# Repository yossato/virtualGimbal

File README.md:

# VirtualGimbal
The VirtualGimbal is an electronic stabilize device for videos that were taken by a hand-held camera such as a DSLR. For more information, see [PetaPixel] ( https://petapixel.com/2016/08/11/sd-card-built-gyro-sensor-stabilize-shots/ "PetaPixel").  The VirtualGimbal consists of an SD card and post-processing software. This repository releases the post-processing software, a SD card circuit and a SD card firmware.

## Demo
<https://youtu.be/NwUnrnFLjD4>

## Features
1.Post-processing video stabilization software on PC.  
2.4K video available.  
3.Stabilization completely based on captured angular velocity data.  

## Requirement
Ubuntu 18.04 or later
FFMPEG, OpenCV3, Eigen, boost and some python libraries.

## Usage  
See post_processing_software/README.md  
Download [Example Video](https://www.dropbox.com/s/y9ugb7c9l8qy5zy/C0003.MP4?dl=1), put in ~/vgdataset. Download [Angular Velocity data](https://www.dropbox.com/s/mz7mn3maapkgodw/2019-04-03_07.27.36.json?dl=1) and put it in virtualGimbal/post_processing_software/build/records. A camera calibration file also required to run a demo below so download [Calibration file](https://www.dropbox.com/s/we9r2a2w1un4lyf/cameras.json?dl=1) then put it in virtualGimbal/post_processing_software/build/camera_descriptions    

Demo:  
```
./pixelwise_stabilizer -i ~/vgdataset/C0003.MP4 -c ILCE-6500 -l SEL1670Z -j records/2019-04-03_07.27.36.json -z 1.3 -o  
```

Here, `i` option is an input video file. `c` is a camera name that is calibrated using a calibrator. `l` is a lens name. `j` is a json file that include an angular velocity record of a gyro sensor. `z` is a zooming ratio. Recommended zooming ratio is 1.3 . `o` option outputs stabilized video.  
Additional option `n` is available to disable preview window. This option speed ups the processing.    

Camera calibration is required before you stabilize your own video. See a [detail information](https://github.com/yossato/virtualGimbal/tree/master/post_processing_software) to do it.

## Install dependencies
### Install system dependencies:
```
sudo apt-get install cmake make git  
```

### Install Git:
```
sudo apt install git-all
```  

### Install Python Dev:
```
sudo apt-get install python3-dev python3-pip python3-tk python3-lxml python3-six
```

### Install Numpy & Scipy:
```
sudo apt-get install python3-numpy python3-scipy
```

### Install Matplot Library:
```
sudo apt-get install python3-matplotlib
```

### Install OpenCL: See [detail information](https://github.com/intel/compute-runtime/releases)
```
sudo apt install ocl-icd-libopencl1 opencl-headers clinfo ocl-icd-opencl-dev  

# OPTION: Install intel conpute-runtime with a command below if you use intel HD graphics.
# If you use NVIDIA gpu, it is not required. On the other hand, CUDA is required.
sudo apt-get install intel-opencl-icd
```

### Install ffmpeg:  
```
sudo apt install yasm pkg-config  
cd  
git clone  git://source.ffmpeg.org/ffmpeg.git  
cd ffmpeg
git checkout -b tag refs/tags/n4.4
./configure --enable-gpl --enable-x86asm --enable-opencl --enable-ffmpeg --enable-pic --enable-shared --disable-static --enable-swscale
make all -j4  
sudo make install  
sudo ldconfig  
```

### Install OpenCV  
```
cd  
sudo apt-get install build-essential module-assistant libgtk-3-dev  
sudo m-a prepare  
git clone https://github.com/opencv/opencv.git
cd opencv
git checkout refs/tags/4.5.3
cd opencv/  
  
mkdir build  
cd build  
cmake .. -DWITH_TBB=ON -DWITH_OPENGL=ON -DWITH_VTK=ON -DWITH_GTK=ON  -DWITH_FFMPEG=ON -DCMAKE_BUILD_TYPE=Release    
make -j4  
sudo make install  

sudo sh -c "echo /usr/local/lib >> /etc/ld.so.conf.d/opencv.conf"  
sudo sh -c "echo PKG_CONFIG_PATH=\\\$PKG_CONFIG_PATH:/usr/local/lib/pkgconfig >> /etc/bash.bashrc"  
sudo sh -c "echo export PKG_CONFIG_PATH >> /etc/bash.bashrc"  
```

### Install Eigen
```
sudo apt install libeigen3-dev  
```

## Build
```
cd
git clone https://github.com/yossato/virtualGimbal.git  
cd virtualGimbal  
mkdir build  
cd build  
cmake ../post_processing_software/ -DCMAKE_BUILD_TYPE=Release  
make -j4  
```

## To start up faster  
I added a program angular_velocity_estimator that generates a JSON file. The file will be saved in same directory of video file after execution.
If the file exists, the pixelwise_stabilizer starts up faster.
To run the program, execute a command like below.
```  
./angular_velocity_estimator ~/vgdataset/C0003.MP4  
```  
  
This command generates C0003.json .

The file contains estimated angular velocity from the video that is used for synchronizing between video and angular velocity measured by the gyro sensor.

## Contribution

## Todo
- Speeding up
- Brushing up deblur quality

## Author
Yoshiaki Sato

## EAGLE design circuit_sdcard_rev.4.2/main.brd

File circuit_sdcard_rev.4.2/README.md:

## License  
Copyright (c) 2018, Yoshiaki Sato  
<br />This work is licensed under a <a rel="license" href="http://creativecommons.org/licenses/by-sa/4.0/">Creative Commons Attribution-ShareAlike 4.0 International License</a>.  

# This circuit is SD card virsion.

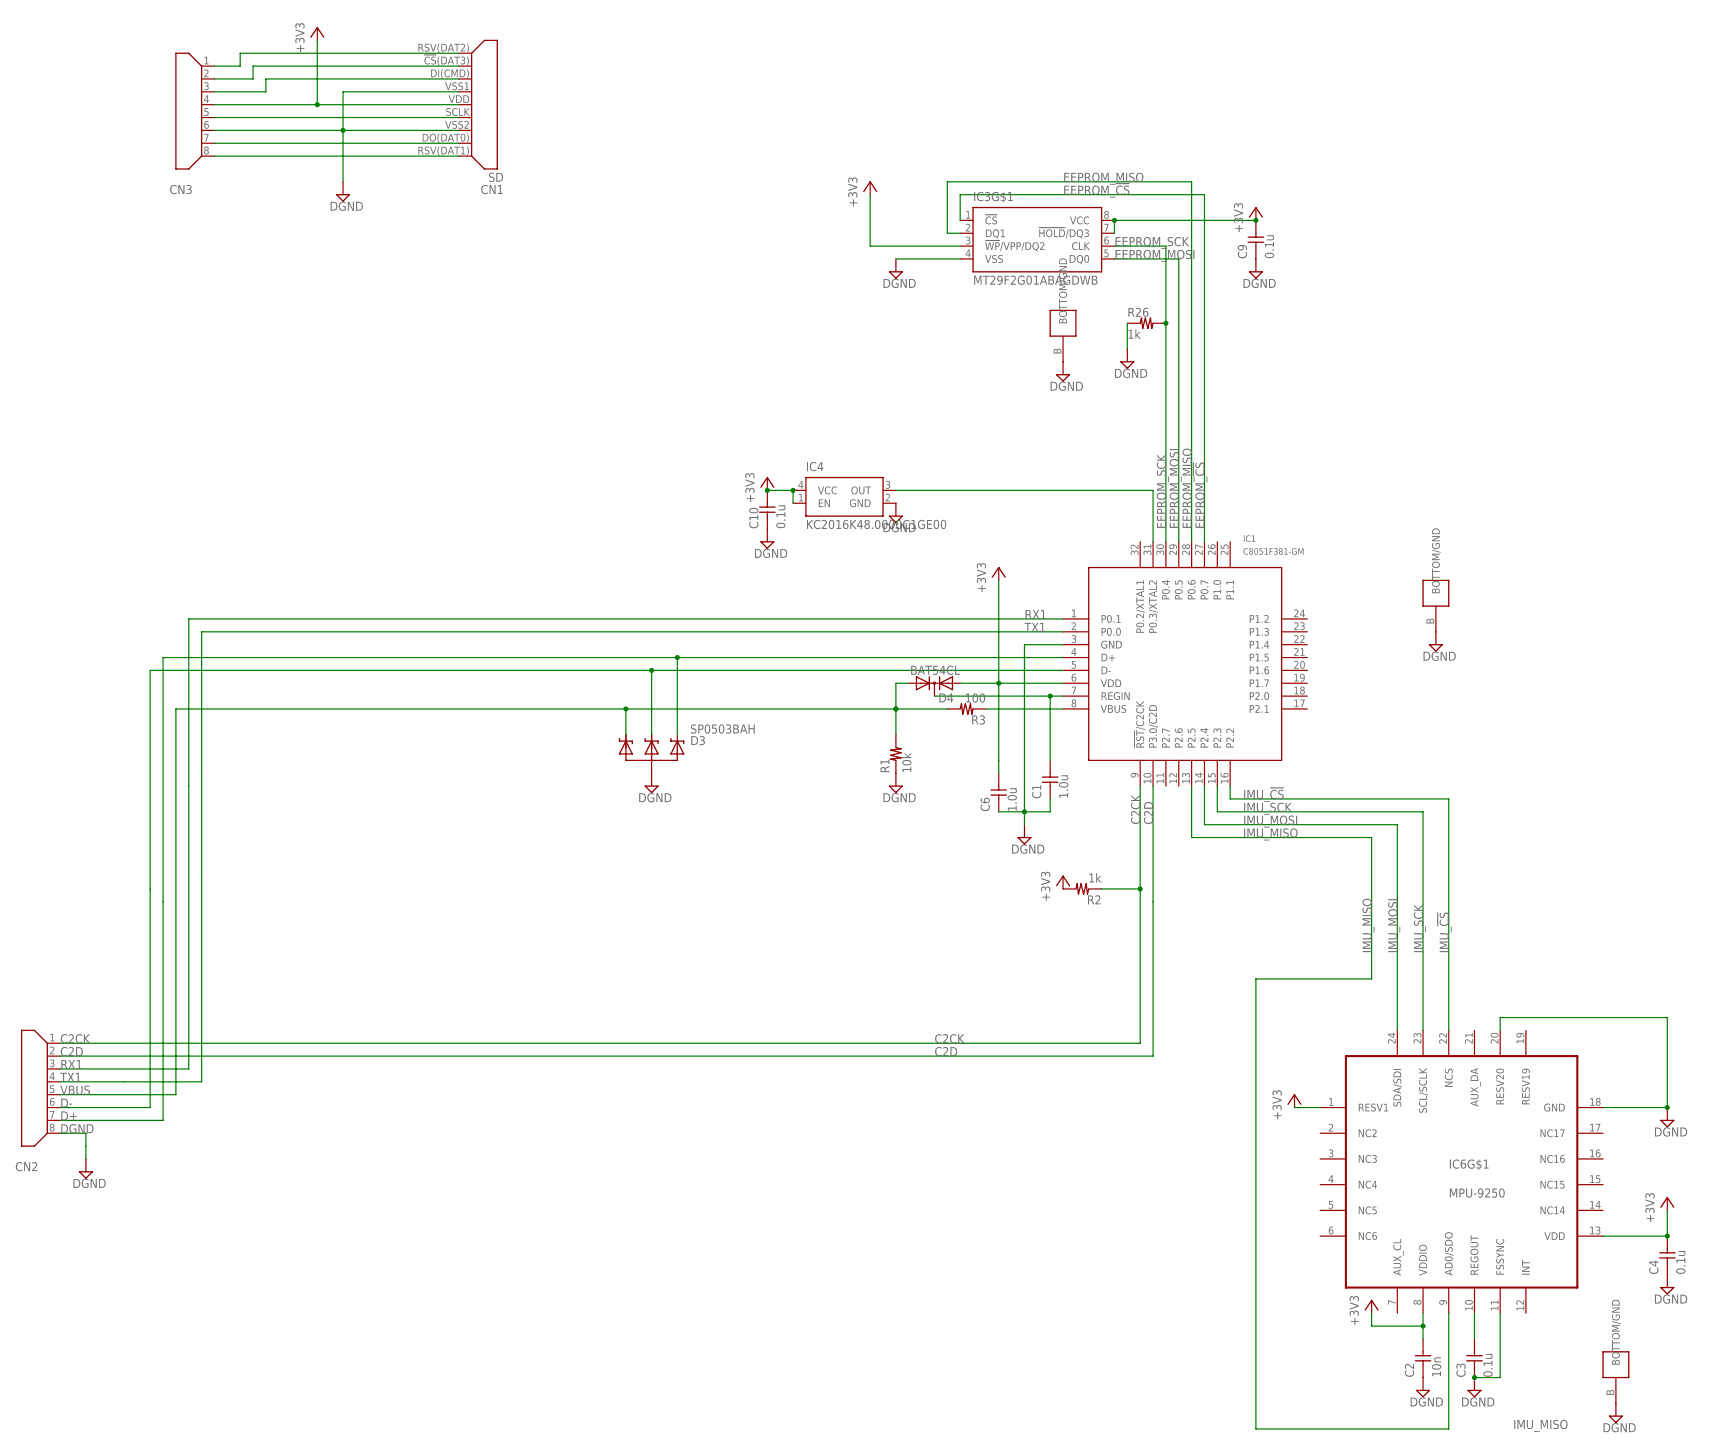
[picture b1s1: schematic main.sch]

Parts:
C1, C6: 1.0u; 1005
C2: 10n; 1005
C3, C4, C9, C10: 0.1u; 1005
CN1: SD; SD_V3
CN2, CN3: MICROSD; BLOCK_SD_CONNECTOR
D3: SP0503BAH; SOT143
D4: BAT54CL; SOT23
IC1: C8051F381-GM; QFN32
IC3: MT29F2G01ABAGDWB; V-PDFN-8
IC4: KC2016K48.0000C1GE00; KC2016K
IC6: MPU-9250; QFN-24
R1: 10k; 1005
R2, R26: 1k; 1005
R3: 100; 1005

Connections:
+3V3: C2.P$2, C4.P$2, C6.P$2, C9.P$2, C10.P$2, CN1.VDD, CN3.4, D4.2 (A2), IC1.6 (VDD), IC3.3 (!WP!/VPP/DQ2), IC3.7 (!HOLD!/DQ3), IC3.8 (VCC), IC4.1 (EN), IC4.4 (VCC), IC6.1 (RESV1), IC6.8 (VDDIO), IC6.13 (VDD), R2.P$2
C2CK: CN2.1, IC1.9 (!RST!/C2CK), R2.P$1
C2D: CN2.2, IC1.10 (P3.0/C2D)
D+: CN2.7, D3.2, IC1.4 (D+)
D-: CN2.6, D3.3, IC1.5 (D-)
DGND: C1.P$1, C2.P$1, C3.P$1, C4.P$1, C6.P$1, C9.P$1, C10.P$1, CN1.VSS1, CN1.VSS2, CN2.8, CN3.6, D3.1, IC1.3 (GND), IC1.B (BOTTOM/GND), IC3.4 (VSS), IC3.B (BOTTOM/GND), IC4.2 (GND), IC6.11 (FSSYNC), IC6.18 (GND), IC6.20 (RESV20), IC6.B (BOTTOM/GND), R1.P$1, R26.P$1
EEPROM_!CS: IC1.27 (P0.7), IC3.1 (!CS)
EEPROM_MISO: IC1.28 (P0.6), IC3.2 (DQ1)
EEPROM_MOSI: IC1.29 (P0.5), IC3.5 (DQ0)
EEPROM_SCK: IC1.30 (P0.4), IC3.6 (CLK), R26.P$2
IMU_!CS: IC1.16 (P2.2), IC6.22 (NCS)
IMU_MISO: IC1.13 (P2.5), IC6.9 (AD0/SDO)
IMU_MOSI: IC1.14 (P2.4), IC6.24 (SDA/SDI)
IMU_SCK: IC1.15 (P2.3), IC6.23 (SCL/SCLK)
unnamed: C1.P$2, D4.3 (C), IC1.7 (REGIN)
unnamed: CN1.RSV(DAT1), CN3.8
unnamed: CN1.DO(DAT0), CN3.7
unnamed: IC1.8 (VBUS), R3.P$1
unnamed: CN1.SCLK, CN3.5
unnamed: CN1.DI(CMD), CN3.3
unnamed: IC1.31 (P0.3/XTAL2), IC4.3 (OUT)
unnamed: CN1.!CS!(DAT3), CN3.2
unnamed: C3.P$2, IC6.10 (REGOUT)
unnamed: CN1.RSV(DAT2), CN3.1
RX1: CN2.3, IC1.1 (P0.1)
TX1: CN2.4, IC1.2 (P0.0)
VBUS: CN2.5, D3.4, D4.1 (A1), R1.P$2, R3.P$2

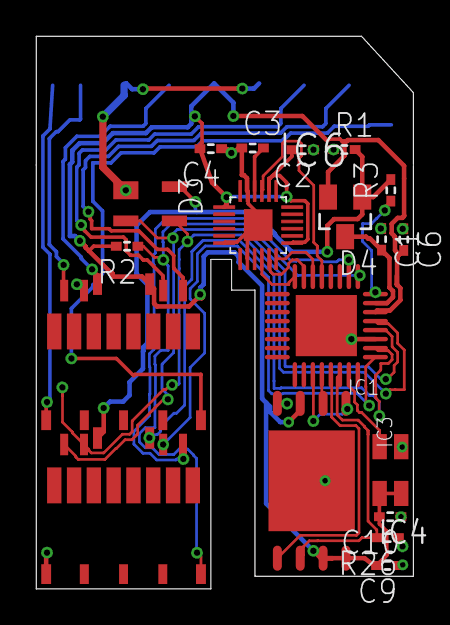
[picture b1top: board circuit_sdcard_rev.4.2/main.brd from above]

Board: 2 copper layers, 20.9 x 30.7 mm, 20 parts (1 on the bottom side), 27 nets.

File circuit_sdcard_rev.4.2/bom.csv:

"Part";"Value";"Device";"Package";"Description";"";
"C1";"1.0u";"C-1005";"1005";"";"";
"C2";"10n";"C-1005";"1005";"";"";
"C3";"0.1u";"C-1005";"1005";"";"";
"C4";"0.1u";"C-1005";"1005";"";"";
"C6";"1.0u";"C-1005";"1005";"";"";
"C9";"0.1u";"C-1005";"1005";"";"";
"C10";"0.1u";"C-1005";"1005";"";"";
"CN1";"SD";"SD";"SD_V3";"";"";
"CN2";"";"MICROSD";"BLOCK_SD_CONNECTOR";"";"";
"CN3";"";"MICROSD";"BLOCK_SD_CONNECTOR";"";"";
"D3";"SP0503BAH";"SP0503BAH";"SOT143";"";"";
"D4";"BAT54CL";"HSMS-2854";"SOT23";"Surface Mount Microwave Schottky Detector Diodes";"";
"IC1";"C8051F381-GM";"C8051F381-GM";"QFN32";"";"";
"IC3";"MT29F2G01ABAGDWB";"N25Q512A";"V-PDFN-8";"";"";
"IC4";"KC2016K48.0000C1GE00";"KC2016K";"KC2016K";"";"";
"IC6";"MPU-9250";"MPU-9250";"QFN-24";"";"";
"R1";"10k";"R-1005";"1005";"";"";
"R2";"1k";"R-1005";"1005";"";"";
"R3";"100";"R-1005";"1005";"";"";
"R26";"1k";"R-1005";"1005";"";"";

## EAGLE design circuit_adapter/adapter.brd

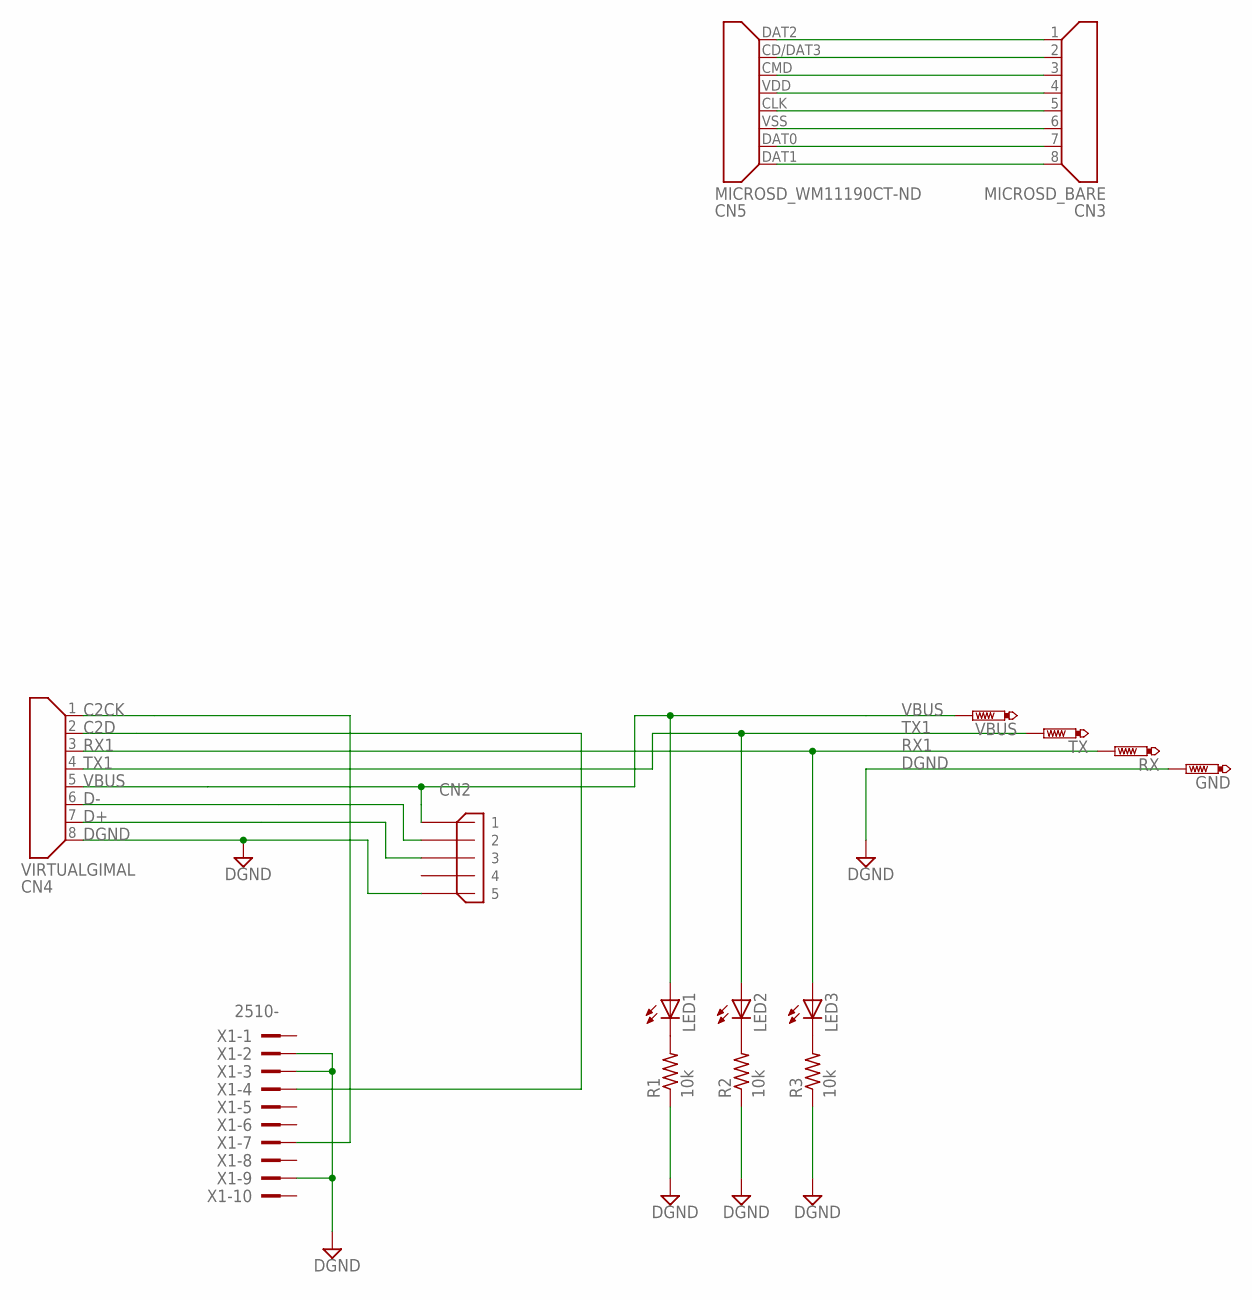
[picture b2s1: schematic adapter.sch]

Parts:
CN2: MICROUSB_ZX62D1-B-5PA(30); ZX62D1-B-5PA(30)
CN3: MICROSD_BARE; MICROSD
CN4: VIRTUALGIMAL; VIRTUALGIMBAL
CN5: MICROSD_WM11190CT-ND; 5033981892
GND: PTR1TP19R; TP19R
LED1, LED2, LED3: LEDSML0603; SML0603
R1, R2, R3: 10k; R0402
RX: PTR1TP19R; TP19R
TX: PTR1TP19R; TP19R
VBUS: PTR1TP19R; TP19R
X1: 2510-; PAK100/2500-10

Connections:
C2CK: CN4.1, X1.7
C2D: CN4.2, X1.4
D+: CN2.3_D+ (3), CN4.7
D-: CN2.2_D- (2), CN4.6
DGND: CN2.5_GND (5), CN4.8, GND.TP, R1.1, R2.1, R3.1, X1.2, X1.3, X1.9
unnamed: LED1.C, R1.2
unnamed: LED2.C, R2.2
unnamed: LED3.C, R3.2
unnamed: CN3.1, CN5.DAT2
unnamed: CN3.2, CN5.CD/DAT3
unnamed: CN3.3, CN5.CMD
unnamed: CN3.4, CN5.VDD
unnamed: CN3.5, CN5.CLK
unnamed: CN3.6, CN5.VSS
unnamed: CN3.7, CN5.DAT0
unnamed: CN3.8, CN5.DAT1
RX1: CN4.3, LED3.A, RX.TP
TX1: CN4.4, LED2.A, TX.TP
VBUS: CN2.1_VCC (1), CN4.5, LED1.A, VBUS.TP

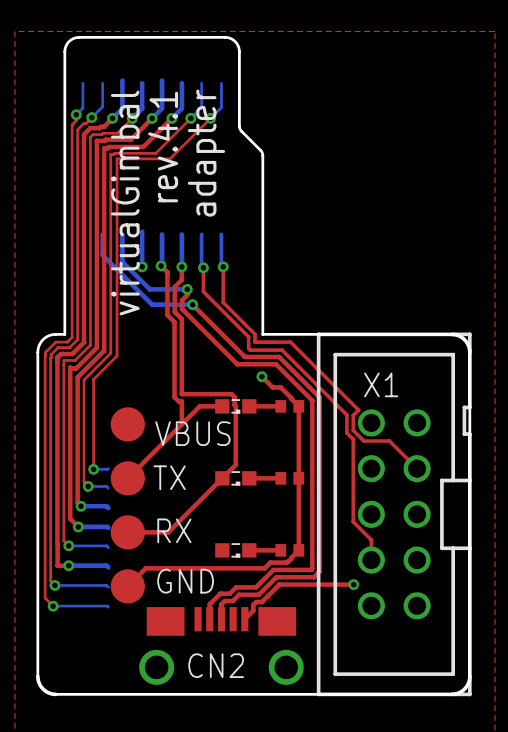
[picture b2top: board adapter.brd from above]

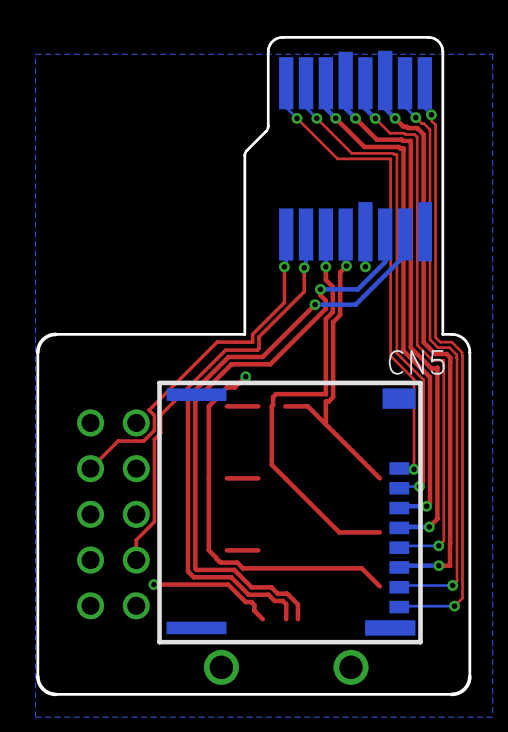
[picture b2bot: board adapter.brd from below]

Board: 2 copper layers, 24.0 x 36.5 mm, 15 parts (3 on the bottom side), 19 nets.

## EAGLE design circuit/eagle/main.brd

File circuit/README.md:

## License  
Copyright (c) 2018, Yoshiaki Sato  
All rights reserved.  

<br />This work is licensed under a <a rel="license" href="http://creativecommons.org/licenses/by-sa/4.0/">Creative Commons Attribution-ShareAlike 4.0 International License</a>.

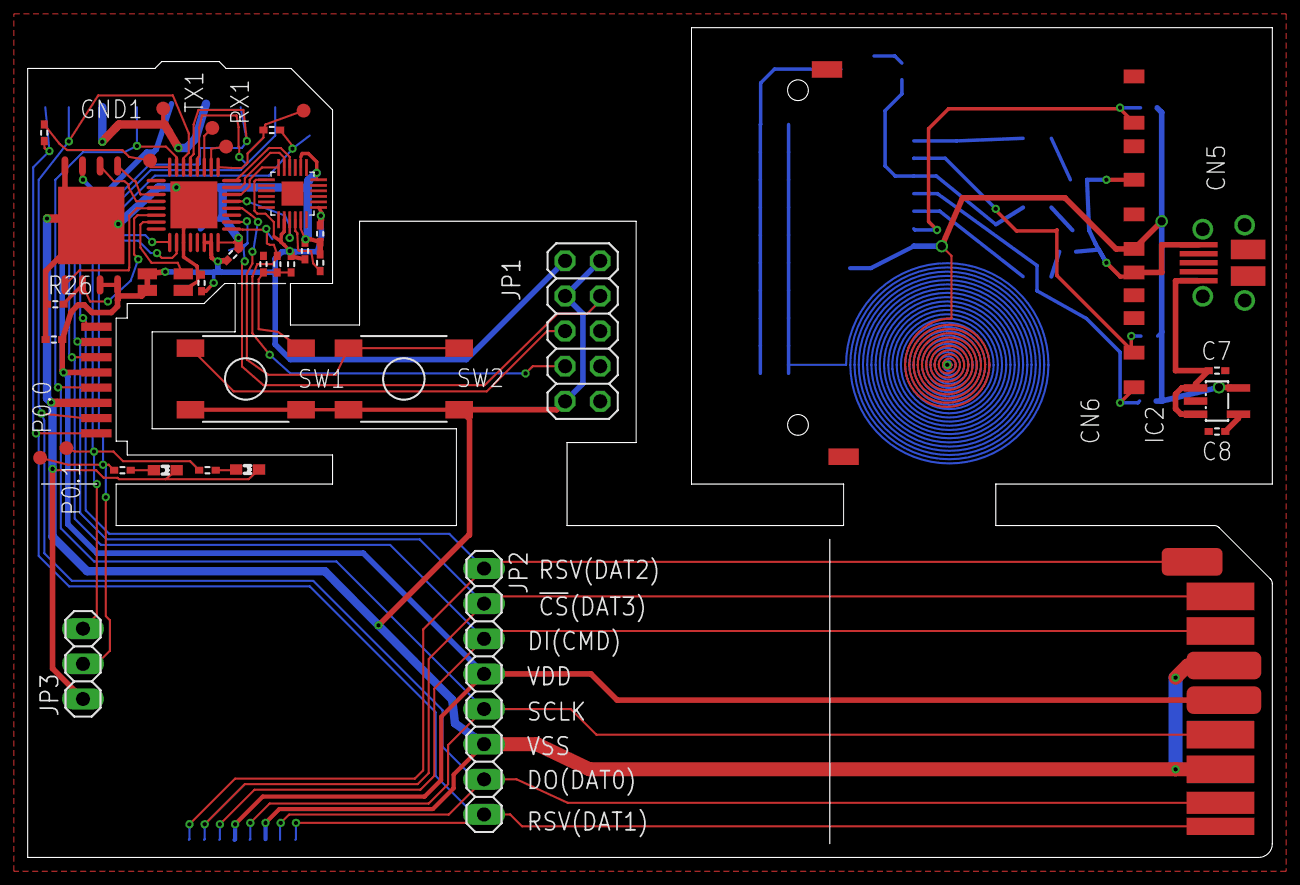
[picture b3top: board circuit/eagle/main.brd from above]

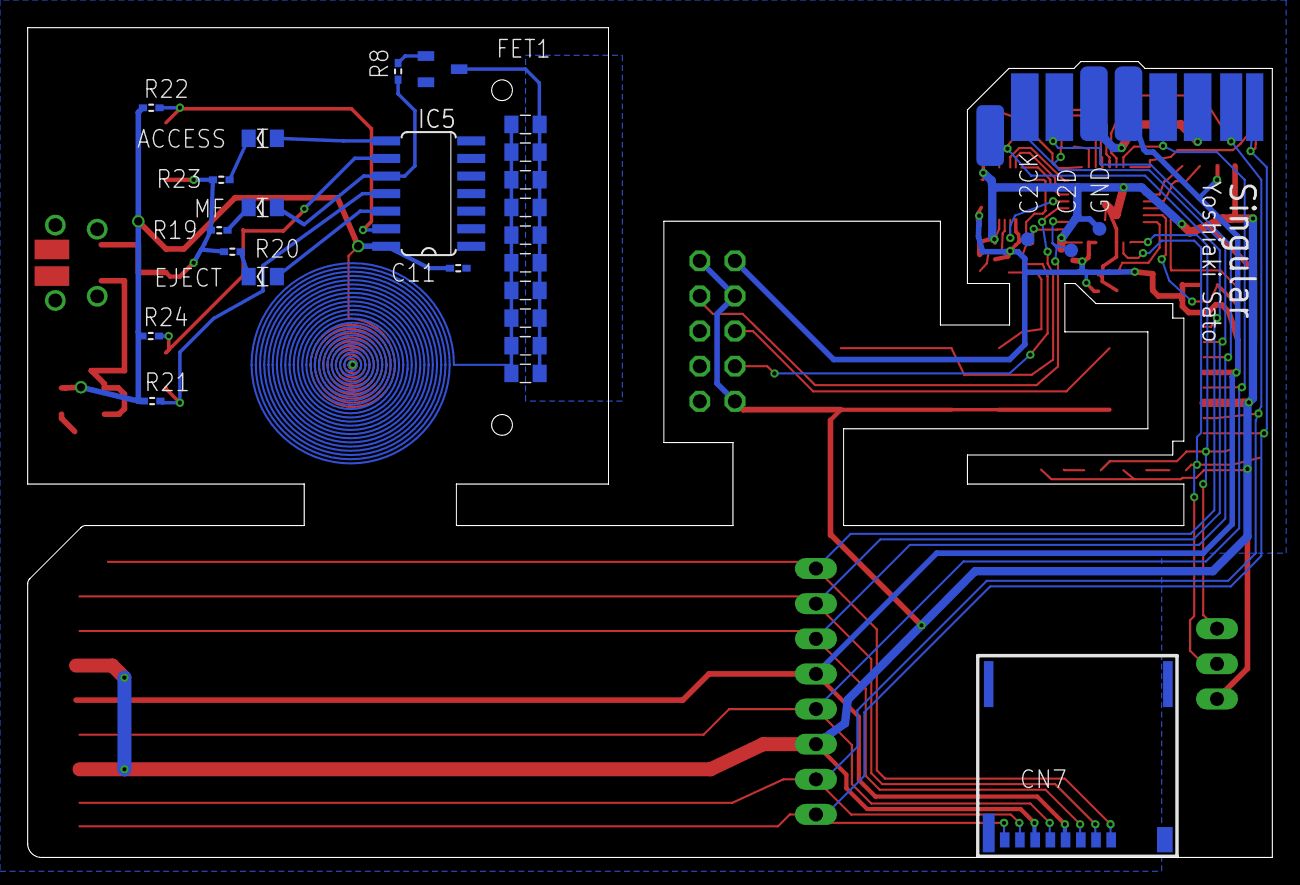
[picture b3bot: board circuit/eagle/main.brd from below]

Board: 2 copper layers, 90.0 x 60.0 mm, 67 parts (28 on the bottom side), 45 nets.

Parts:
ACCESS: 2012
C1, C6: 1.0u; 1005
C2: 10n; 1005
C2CK, C2D: PTR1TP10R; TP10R
C3, C4, C7, C9, C10, C11: 0.1u; 1005
C8: 0.01u; 1005
CN1: MICROSD
CN3, CN4: SD
CN5: MICROUSB(10103594-0001LF)
CN6: SD_WP_CD; 10067847-001RLF
CN7: MICROSD_WM11190CT-ND; 5033981892
EJECT: 2012
FET1: DMN3404L; SOT23
GND, GND1: PTR1TP10R; TP10R
GREEN_LED: PTR1TP10R; TP10R
IC1: C8051F381-GM; QFN32
IC2: SOT23
IC3: N25Q512A; V-PDFN-8
IC4: KC2016K
IC5: 74HC14D; SO14
IC6: MPU-9250; QFN-24
JP1: 2X05
JP2: 1X08
JP3: 1X03
LED1, LED2: 1608-OLI
MAG: PTR1TP10R; TP10R
MF: 2012
P0.0, P0.1: PTR1TP10R; TP10R
R1, R2, R26: 1k; 1005
R3, R4: 10k; 1005
R6, R7: 5.1k; 1005
R8: 100; 1005
R9, R10, R11, R12, R13, R14, R15, R16, R17, R18: 2012
R19, R20, R23: 1005
R21, R22, R24: 330k; 1005
RX1: PTR1TP10R; TP10R
SW1, SW2: 2X2(SUZUSYO2)
TX1: PTR1TP10R; TP10R

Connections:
+3V3: C2.P$2, C4.P$2, C6.P$2, C9.P$2, C10.P$2, CN1.VDD, CN3.VDD, CN4.VDD, CN7.VDD, IC1.6, IC1.7, IC3.3, IC3.7, IC3.8, IC4.1, IC4.4, IC6.1, IC6.8, IC6.13, JP1.1, JP2.4, R1.P$2
+5V: C7.P$2, CN5.1, IC2.1, IC2.3
C2CK: C2CK.TP, IC1.9, JP1.7, R2.P$1
C2D: C2D.TP, IC1.10, JP1.4
DGND: C1.P$1, C2.P$1, C3.P$1, C4.P$1, C6.P$1, C7.P$1, C8.P$1, C9.P$1, C10.P$1, C11.P$1, CN1.VSS, CN3.VSS1, CN3.VSS2, CN4.VSS1, CN4.VSS2, CN5.5, CN6.GND1, CN6.GND2, CN6.VSS1, CN6.VSS2, CN7.VSS, FET1.S, GND.TP, GND1.TP, IC1.3, IC1.8, IC1.B, IC2.2, IC3.4, IC3.B, IC4.2, IC5.1, IC5.3, IC5.5, IC5.7, IC6.11, IC6.18, IC6.20, JP1.2, JP1.3, JP1.9, JP2.6, JP3.1, LED1.K, LED2.K, R19.P$1, R20.P$1, R23.P$1, R26.P$1, SW1.D1, SW1.D2, SW2.D1, SW2.D2
EEPROM_!CS: IC1.27, IC3.1
EEPROM_MISO: IC1.28, IC3.2
EEPROM_MOSI: IC1.29, IC3.5
EEPROM_SCK: IC1.30, IC3.6, R26.P$2
GREEN_LED: CN1.RSV(DAT1), CN3.RSV(DAT1), CN4.RSV(DAT1), CN7.DAT1, JP2.8, R4.P$1
IMU_!CS: IC1.16, IC6.22
IMU_MISO: IC1.13, IC6.9
IMU_MOSI: IC1.14, IC6.24
IMU_SCK: IC1.15, IC6.23
MAGNET_EN: CN1.RSV(DAT2), CN3.RSV(DAT2), CN4.RSV(DAT2), CN7.DAT2, JP2.1, R3.P$1
unnamed: IC1.19, TX1.TP
unnamed: IC1.18, RX1.TP
unnamed: JP1.5, SW1.U1
unnamed: IC1.1, JP3.3, P0.1.TP, R6.P$2
unnamed: LED2.A, R6.P$1
unnamed: GREEN_LED.TP, IC1.24, R4.P$2
unnamed: EJECT.P$2, R20.P$2
unnamed: LED1.A, R7.P$1
unnamed: C8.P$2, IC2.4
unnamed: IC1.31, IC4.3
unnamed: IC1.12, SW2.U1, SW2.U2
unnamed: C3.P$2, IC6.10
unnamed: IC1.17, MAG.TP, R3.P$2
unnamed: IC1.2, JP3.2, P0.0.TP, R7.P$2
unnamed: IC5.10, MF.P$1, R8.P$1
unnamed: CN6.DAT2, IC5.11, R21.P$2
unnamed: EJECT.P$1, IC5.12
unnamed: CN6.DAT1, IC5.13, R22.P$2
unnamed: FET1.G, R8.P$2
unnamed: FET1.D, R9.P$1, R10.P$1, R11.P$1, R12.P$1, R13.P$1, R14.P$1, R15.P$1, R16.P$1, R17.P$1, R18.P$1
unnamed: ACCESS.P$2, R23.P$2
unnamed: MF.P$2, R19.P$2
unnamed: ACCESS.P$1, IC5.8
unnamed: CN6.!CS!/DAT3, IC5.9, R24.P$2
unnamed: C1.P$2, R1.P$1, R2.P$2, SW1.U2
SPI_!CS: CN1.!CS!(DAT3), CN3.!CS!(DAT3), CN4.!CS!(DAT3), CN7.CD/DAT3, IC1.20, JP2.2
SPI_MISO: CN1.DO(DAT0), CN3.DO(DAT0), CN4.DO(DAT0), CN7.DAT0, IC1.22, JP2.7
SPI_MOSI: CN1.DI(CMD), CN3.DI(CMD), CN4.DI(CMD), CN7.CMD, IC1.21, JP2.3
SPI_SCK: CN1.SCLK, CN3.SCLK, CN4.SCLK, CN7.CLK, IC1.23, JP2.5
VDD: C11.P$2, CN6.VDD, IC2.5, IC5.14, R9.P$2, R10.P$2, R11.P$2, R12.P$2, R13.P$2, R14.P$2, R15.P$2, R16.P$2, R17.P$2, R18.P$2, R21.P$1, R22.P$1, R24.P$1

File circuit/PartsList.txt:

Partlist

Part      Value                     Package                   Library    Position (mm)         Orientation

ACCESS                              2012                      LED        (73 25)               MR180
C1        1.0u                      1005                      reg,cap    (17.05 15.9)          R270
C2        10n                       1005                      reg,cap    (20.05 16.85)         R270
C2CK      PTR1TP10R                 TP10R                     testpad    (17.7 17.7)           MR0
C2D       PTR1TP10R                 TP10R                     testpad    (14.55 16.9)          MR0
C3        0.1u                      1005                      reg,cap    (21.15 16)            R270
C4        0.1u                      1005                      reg,cap    (21.15 18.1)          R90
C6        1.0u                      1005                      reg,cap    (14.8414 16.6)        R225
C7        0.1u                      1005                      reg,cap    (86 8.2)              R180
C8        0.01u                     1005                      reg,cap    (86 3.8)              R0
C9        0.1u                      1005                      reg,cap    (1.9 10.45)           R0
C10       0.1u                      1005                      reg,cap    (12.5708 14.5415)     R270
C11       0.1u                      1005                      reg,cap    (58.8664 15.6096)     MR180
CN1       MICROSD                   MICROSD                   Connector  (6.24 11.37)          R0
CN3       SD                        SD                        Connector  (20.4 25.25)          MR0
CN4       SD                        SD                        Connector  (84.25 -5.625)        R270
CN5       MICROUSB(10103594-0001LF) MICROUSB(10103594-0001LF) Connector  (88 16)               R90
CN6       SD_WP_CD                  10067847-001RLF           Connector  (80 7)                R270
CN7       MICROSD_WM11190CT-ND      5033981892                Connector  (7.2 -12.8)           MR180
EJECT                               2012                      LED        (73 15)               MR180
FET1      DMN3404L                  SOT23                     MOSFET     (60 30)               MR270
GND       PTR1TP10R                 TP10R                     testpad    (12.5 18.45)          MR0
GND1      PTR1TP10R                 TP10R                     testpad    (9.8 27.15)           R0
GREEN_LED PTR1TP10R                 TP10R                     testpad    (8.85 23.4)           R0
IC1       C8051F381-GM              QFN32                     C8051F34x  (12.02 20.19)         R90
IC2                                 SOT23                     linear     (86 6)                R270
IC3       N25Q512A                  V-PDFN-8                  EEPROM     (4.6 18.7)            R270
IC4       KC2016K                   KC2016K                   Oscillator (9.95 14.6)           R0
IC5       74HC14D                   SO14                      74xx       (61 21)               MR90
IC6       MPU-9250                  QFN-24                    GYRO       (19.15 21)            R0
JP1                                 2X05                      pinhead    (40.13 11.06)         R270
JP2                                 1X08                      pinhead    (33 -15)              R270
JP3                                 1X03                      pinhead    (4 -13)               R90
LED1                                1608-OLI                  LED        (9.95 1)              R0
LED2                                1608-OLI                  LED        (15.9 1.05)           R0
MAG       PTR1TP10R                 TP10R                     testpad    (19.95 27)            R0
MF                                  2012                      LED        (73 20)               MR180
P0.0      PTR1TP10R                 TP10R                     testpad    (0.9 1.9)             R0
P0.1      PTR1TP10R                 TP10R                     testpad    (2.8 2.6)             R0
R1        1k                        1005                      reg,cap    (19.05 15.9)          R90
R2        1k                        1005                      reg,cap    (18.05 15.9)          R270
R3        10k                       1005                      reg,cap    (17.65 25.6)          R180
R4        10k                       1005                      reg,cap    (1.2 25.4)            R90
R6        5.1k                      1005                      reg,cap    (13 1)                R180
R7        5.1k                      1005                      reg,cap    (6.85 1)              R180
R8        100                       1005                      reg,cap    (63.2128 29.84)       MR90
R9                                  2012                      reg,cap    (54 8)                MR180
R10                                 2012                      reg,cap    (54 10)               MR180
R11                                 2012                      reg,cap    (54 12)               MR180
R12                                 2012                      reg,cap    (54 14)               MR180
R13                                 2012                      reg,cap    (54 16)               MR180
R14                                 2012                      reg,cap    (54 18)               MR180
R15                                 2012                      reg,cap    (54 20)               MR180
R16                                 2012                      reg,cap    (54 22)               MR180
R17                                 2012                      reg,cap    (54 24)               MR180
R18                                 2012                      reg,cap    (54 26)               MR180
R19                                 1005                      reg,cap    (76.15 18.35)         MR0
R20                                 1005                      reg,cap    (75.2 16.8)           MR0
R21       330k                      1005                      reg,cap    (81 6)                MR0
R22       330k                      1005                      reg,cap    (81.068 27.2064)      MR0
R23                                 1005                      reg,cap    (76 22)               MR0
R24       330k                      1005                      reg,cap    (81.1 10.7)           MR0
R26       1k                        1005                      reg,cap    (2 13)                R0
RX1       PTR1TP10R                 TP10R                     testpad    (14.35 24.4)          R0
SW1       2X2(SUZUSYO2)             2X2(SUZUSYO2)             Switch     (15.77 7.6)           R0
SW2       2X2(SUZUSYO2)             2X2(SUZUSYO2)             Switch     (27.2 7.6)            R0
TX1       PTR1TP10R                 TP10R                     testpad    (13.35 25.75)         R0

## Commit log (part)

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2019-01-06 modified .gitignore
2019-01-06 post_processing_software: Modified script name
2019-01-06 post_processing_software: Succeeded reading angular velocity from virtualGimbal using python script and save json file that contains angular velocity
2019-01-07 post_processing_software: Added rapidjson sample code
2019-01-09 post_processing_software: Modified rapidjson_test.cpp
2019-01-11 firmware_sdcard_rev.4.1: Fix data visualize
2019-01-12 firmware_sdcard_rev.4.1: Added LICENSE
2019-01-12 Update LICENSE
2019-01-13 post_processing_software: Added optical flow getter
2019-01-16 post_processing_software: Temporary error handling, named_plot crashs
2019-01-19 post_processing_software: Removing black space
2019-01-21 post_processing_software: Modifing build error
2019-01-22 post_processing_software: fixing hasBlackSpace function
2019-01-23 post_processing_software: Fix filter culclation
2019-01-23 post_processing_software: Complete calculation of adaptive filter strength
2019-01-25 post_processing_software: Successfully removed black space. Added variable filter coefficient.
2019-01-25 post_processing_software: Modified graph title of debug mode
2019-01-26 post_processing_software:Added video analyzer.cpp
2019-01-27 post_processing_software: Added json parser for optical flow read and write
2019-01-29 post_processing_software: Add synchronized quaternion read and write
2019-01-30 PCB files upload
    Added old PCB files for ease and tracking
2019-01-31 post_processing_software: Adding -j option to read angular velocity from virtual gimbal
2019-02-07 post_processing_software: Added cameras.json
2019-02-09 post_processing_software: Added camera info parser
2019-02-09 post_processing_software: Added camera infomation but contains an distortion error
2019-02-09 post_processing_software: Fix undistort bug
2019-02-10 post_processing_software:Added writeCameraInformationJson function
2019-02-12 post_processing_software: Modifing calibration tool
2019-02-12 post_processing_software: Added sd card rotation setting
2019-02-14 post_processing_software: Modified writeCameraInformationJson function to realize add multi camera calibration parameters to json file
2019-02-14 post_processing_software: Added lens and image size check
2019-02-15 post_processing_software: Enabled multi json angular velocity input
2019-02-15 post_processing_software: Modify log
2019-02-16 post_processing_software: Modify json sample name and added sd_card_rotation.png
2019-02-16 post_processing_software: Fix scripts and ini file
2019-02-17 post_processing_software: Modified connect_via_usb.jpg
2019-02-17 post_processing_software: Added connector.jpg
2019-02-17 post_processing_software: Modified sd card rotation image
2019-02-18 Update README.md
    Updated ReadMe with clearer install instructions & more accurate dependency requirements.
2019-02-18 Update README.md
    Updated build instructions with modern directory names.
2019-02-19 Grammar
    Updates to the grammer and litteracy of the text.
2019-02-20 4.1 Integration
    Integration of the new 4.1 Revision
2019-02-21 firmware_sdcard_rev.4.1: Added writable page region finder
2019-02-24 Revert "firmware_sdcard_rev..1: Added writable page region finder"
    This reverts commit be23c4f9d5582fbfb0e75fc9b77b8a8334889173.
2019-02-24 firmware_sdcard_rev.4.1:Fixing firmware
2019-02-25 firmware_sdcard_rev.4.1: Fixing recording algorithm
2019-02-27 firmware_sdcard_rev.4.1: Fix log
2019-02-27 post_processing_software: Added erace python script.
2019-02-28 firmware_sdcard_rev4.1: Fix LED turn of sequence
2019-03-01 firmware_sdcard_rev.4.1: Fix frame rate drop and increase recode frame rate to 240 Hz
2019-03-01 firmware_sdcard_rev.4.1: add first firmware binary
2019-03-01 post_processing_software: Add erasing script
2019-03-01 firmware_sdcard_rev.4.1: Fix json bug and replace binary
2019-03-01 post_processing_software: Fix frequency of main function and remove unused param on json
2019-03-06 firmware_sdcard_rev.4.1: Fix clock source
2019-03-06 post_processing_software: Modified sampling rate from 60hz to 240hz, and show matching result
2019-03-06 firmware_sdcard_rev.4.1: Fix sampling rate of binary
2019-03-07 post_processing_software: Added quality check tool and reading sampling rate of gyro from a json file
2019-03-08 Update texture.cpp
    Stabilization algorithm improvement
2019-03-09 post_processing_software: Remove unused code.
2019-03-14 post_processing_software: fix black space detection bug
2019-03-18 3D Files
    Attempt to render the main PCB in 3D among with making the schematics more accessible.
2019-03-21 post_processing_software: Adding data class
2019-03-21 post_processing_software: fix dependency
2019-03-21 post_processing_software: Added virtual gimbal manager
2019-03-22 post_processing_software: Modifing manager
2019-03-23 post_processing_software: Fix setEstimatedAngularVelocity function
2019-03-23 post_processing_software: Modified BaseParam
2019-03-23 Add comment
2019-03-29 post_processing_software: Modified permission
2019-04-07 post_processing_software: Add gradient setting
2019-04-09 post_processing_software: Succeed to estimate angular velocity from chess board
2019-04-10 post_processing_software: Modified resampler
2019-04-11 post_processing_software: Calcurate correlation value
2019-04-25 post_processing_software: Succeed show correlation coeffs and measured and estimated angular velocity
2019-04-26 post_processing_software: Fix plot
2019-04-26 post_processing_software: Succeed syncronize estimated and measured angular velocity
2019-04-29 post_processing_software: Added getRotationQuaterion function that return slerped angle
2019-04-30 post_processing_software: Debuged getRotationQuaterion function
2019-04-30 post_processing_software: Added getUndistortUnrollingChessBoardPoints
2019-05-02 post_processing_software: Modified timing
2019-05-16 post_processing_software: Rolling Shutter param successfully estimated
2019-05-18 post_processing_software: Add rolling shutter parameters optimizer
2019-05-20 post_processing_software: Add lm param adjuster
2019-05-21 post_processing_software: Modified optimizer
2019-05-22 post_processing_software: Fix optimizer
2019-05-25 post_processing_software: Change parameter name from rolling_shutter_parameter to line_delay
2019-05-25 post_processing_software: Modify
2019-06-06 post_processing_software: Added pixelwise stabilizer
2019-06-07 post_processing_software: Fix
2019-06-08 post_processing_software: Fix axis misalignment
2019-06-10 post_processing_software: Adding SO3Filter
2019-06-13 post_processing_software: Implementing SO3 filter
2019-06-17 post_processing_software:Adding Correction quaternion
2019-06-20 post_processing_software: Modified bisectionMethod
2019-06-20 pps: Added oprerator() to filter
2019-06-21 pps: Modifing
2019-06-25 post_processing_software: Modified Build error
2019-06-27 post_processing_software: Modified setFilterCoefficient
2019-06-28 Modified black space ditector and filter coeff calc
2019-07-02 post_processing_software: Added opencl manager and kernel
2019-07-04 post_processing_software: Adding cl kernel
2019-07-05 post_processing_software: Modifing kernel args
2019-07-05 post_processing_software:Modifing
2019-07-05 post_processing_software: Modifing shader
2019-07-08 post_processing_software: Fixed kernel bug, acheived correct image correction.
2019-07-11 post_processing_software: Fix memory leak
2019-07-11 post_processing_software: Separate getCorrelationCoefficient function
2019-07-15 post_processing_software: Succesfully completed to detect subframe timing and unrolling and undistorting.
2019-07-15 post_processing_software: Modifing exception
2019-07-15 post_processing_software: Successfully got output video
2019-07-16 Modified memory leak
2019-07-17 Revert "3D Files"
    This reverts commit ff8d691305343d47998cacddc23a5a56d9488b68.
2019-07-17 Revert "Update texture.cpp"
    This reverts commit 396a96852908e270276d190bdb0e4436ba756e85.
2019-07-17 Modified README.md
2019-07-17 Revert "PCB files upload"
    This reverts commit 03652ab9f7e84b47b8ee052179ec2ba353f08585.
2019-07-17 Clean up
2019-07-19 Modifing README.md
2019-07-23 post_processing_software: Added angular velocity estimator
2019-07-24 post_processing_software: Modified json reader
2019-07-25 post_processing_software: Modified offset estimation
2019-07-26 post_processing_software: Added clock error estimator
2019-07-26 post_processing_software: Modified error calculation
2019-07-26 post_processing_software: Modified offset
2019-07-27 post_processing_software: Modified frequency estimation error
2019-07-29 post_processing_software: Modified arg processing
2019-08-02 post_processing_software: Modifing multi thread video writer
2019-08-07 post_processing_software: New multi thread video writer properly works
2019-08-09 post_processing_software: Multi thread reader propely works
2019-08-09 Modified README.md and assertion in callShift.cpp
2019-08-10 post_processing_software: Add n option to disable preview window
2019-08-11 Added rev.4.2 hardware
2019-08-11 circuit_sdcard_rev.4.2: Remove old materials
2019-08-12 circuit_sdcard_rev.4.2: Modified SD Card terminal
2019-08-20 Added polyline synchronizer
2019-08-20 Suppress log
2019-08-21 post_processing_software: Modified filter strength calclation measure
2019-08-25 post_processing_software: Add normal distribution filter class
2019-08-26 post_processing_software: Enabled normal distribution filter
2019-08-26 post_processing_software: Modified stabilization bug
2019-08-26 post_processing_software: Removed boost dependency
2019-08-27 post_processing_software: Add error handling to calibrator
2019-08-27 Remove rev.4.1 circuit
2019-09-10 post_processing_software: Modified unit
2019-09-11 post_processing_software: Add getSyncTableOfShortVideo function for short footage
2019-11-22 Modified comments
2020-09-08 Modified cl kernel for OpenCL 1.2
2020-09-08 Modified cl kernel
2020-09-08 Remove cv::ocl::Image2d for writing, NVIDIA doesn't support it
2020-09-08 Modified kernel
2020-11-04 Added inpaint.hpp
2020-11-09 Modified bom
2020-11-09 Improve error message
2020-11-11 Added spin_inpaintint function
2020-11-15 Modifing
2020-11-16 Change output format to AVC1, use mp4 container
    FMP4 video is not supported with Quicktime on Mac, AVC1 is much preferable now.
    I've tested it and it works.
2020-11-17 add include paths, fix `template at` issue
2020-11-21 Modified inpainting spin
2020-11-21 Improve error messages
2020-11-21 Modifid error message of OpenCL
2020-11-23 New kernel successfully works
2020-11-24 Modified kernel parameter
2020-11-24 Modified cl kernel and buffer size
2020-11-25 Remove boost
2020-11-26 Modified
2020-12-04 Update camera_calibration.cpp
    add rotation of sensor
2021-01-24 Modifid
2021-01-24 Added camera_pose_analyzer
2021-02-01 Added pyramid
2021-02-02 Fix color
2021-02-03 Use opencv optical flow
2021-02-22 Adding drawFlowGrid
2021-02-23 Draw grid
2021-02-25 Modified grid
2021-03-04 Modified warp
2021-03-04 Successfully calculated warp and diff
2021-03-17 Modifing stabilizer kernel cpu
2021-05-23 Add createExtrapolateMap function
2021-05-25 Extrapolation works
2021-05-31 Fix argument
2021-05-31 Fix header file name
2021-05-31 Fix function name
2021-05-31 Modified shift calculator to prepare 3d rotation
2021-05-31 Add findFundamentalMat function
2021-07-04 Got right rotation using essential matrix
2021-07-07 use recover pose and get right R and t
2021-07-07 Simplify getting R, t
2021-07-07 Modified calcShiftFromVideo
2021-07-07 Fix confidence but failed
2021-07-07 Fixing
2021-07-24 Update stabilization for no inpaint
2021-07-24 Format code
2021-07-24 Update kernel
2021-07-24 Disable experimental options
2021-08-13 Fix README to fix opencv and ffmpeg build error
2021-08-13 Fix README
2022-10-22 Add visualize function using jupyter notebook, Remove unused old visualizer
2022-10-22 Add new api
2022-11-02 Removed duplicated api
2022-11-03 Fix jupyter
2022-11-03 Fix calcShift algorithm
2022-11-06 Add point pairs json
2022-11-07 Fix note
2022-11-13 Ignore html
2022-11-13 Add analyze function
2022-11-21 Add sync table json
2022-11-21 Remove test code
2022-11-29 Fix bug
2022-12-07 Clean up jupyter
2022-12-13 Adding a4
2022-12-16 Adding new synchronization method
2022-12-25 Add mid point sync
2022-12-25 Fix table
2022-12-26 Add incremental sync
2022-12-27 RANSAC works
